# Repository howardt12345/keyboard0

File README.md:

# [keyboard0 project](https://kb.ht12345.xyz/0)
[![CC BY-NC-SA 4.0][cc-by-nc-sa-shield]][cc-by-nc-sa]

## This project is currently under active development. Everything is subject to change.

### Tenkeyless (TKL) hot-swap mechanical keyboard with macro keys column, 2 rotary encoders, and OLED display

The PCB is designed to use Kailh Hot-swap sockets. The original specifications also wanted a USB hub, which will be implemented through a separate USB hub daughterboard. 

---

[The layout on keyboard layout editor](http://www.keyboard-layout-editor.com/#/gists/689bc560553c37fa0d04dfba9f11ed96)

[Prototype 2 PCB photos on @howardt12345](https://www.instagram.com/p/CYXeXJdg_eP/)

[Details on my keyboard website](https://kb.ht12345.xyz/0)

[QMK Fork](https://github.com/howardt12345/qmk_firmware/tree/ht12345/keyboard0/keyboards/ht12345/keyboard0)

---
## All of the files in this repository, including the PCBs, are provided without liability and without any guarantee with regards to functionality. Any production files and prototypes from this project are provided without warranty of any kind.

---

**This work is licensed under a** [Creative Commons Attribution-NonCommercial-ShareAlike 4.0 International License][cc-by-nc-sa].

[![CC BY-NC-SA 4.0][cc-by-nc-sa-image]][cc-by-nc-sa]

[cc-by-nc-sa]: http://creativecommons.org/licenses/by-nc-sa/4.0/
[cc-by-nc-sa-image]: https://licensebuttons.net/l/by-nc-sa/4.0/88x31.png
[cc-by-nc-sa-shield]: https://img.shields.io/badge/License-CC%20BY--NC--SA%204.0-lightgrey.svg

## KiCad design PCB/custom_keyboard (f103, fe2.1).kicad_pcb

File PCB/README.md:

# keyboard0 PCB designs

## Directories: 

- `/p1`: The 1st prototype, ordered prototypes confirmed NOT working.
- `/p2`: The 2nd prototype, which I produced a batch of 2 prototypes and they worked (see respective readme)
- `/p3`: The 3rd prototype, under active development and NOT YET TESTED.
- `/Plate`: FR4 plate designs.

Any KiCad files in *this specific directory* is under active development and is subject to change. 

### These PCB designs are provided without liability and without any guarantee with regards to functionality. While I have personally tested some of the designs, I do not guarantee that they will work if you were to produce them yourself.

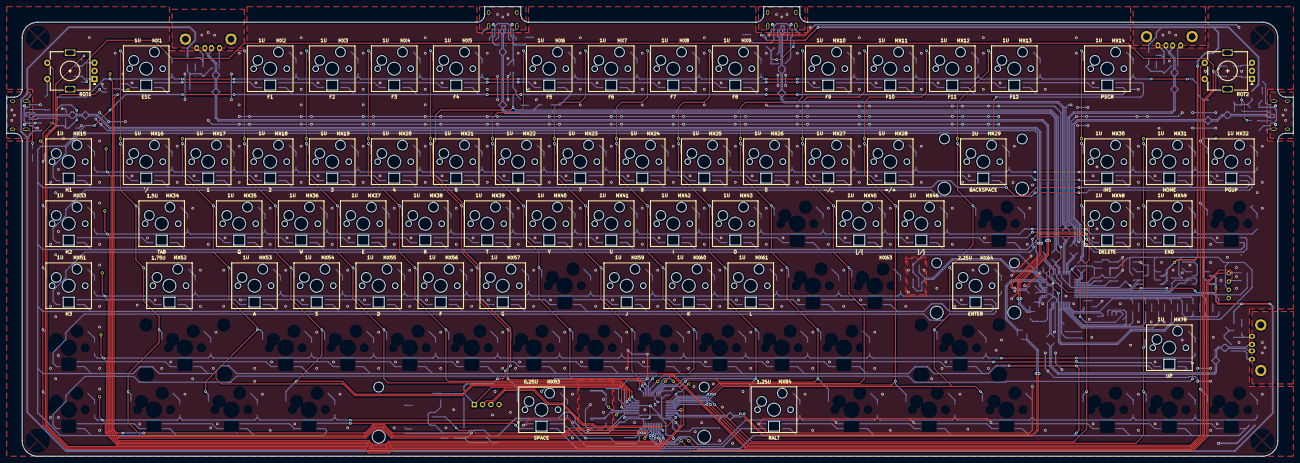
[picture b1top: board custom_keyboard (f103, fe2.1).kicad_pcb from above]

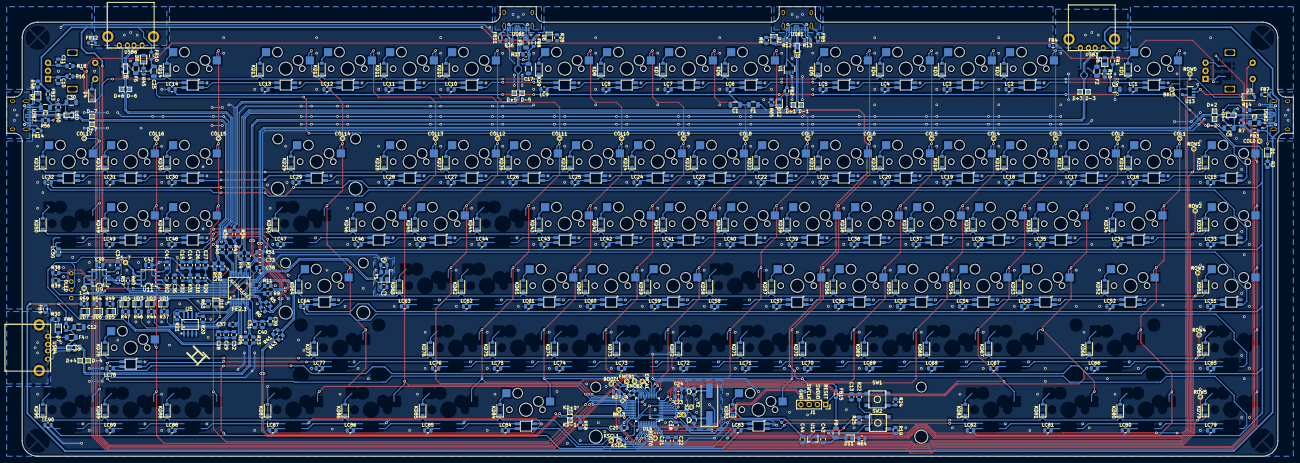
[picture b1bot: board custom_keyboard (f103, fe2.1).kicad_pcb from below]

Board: 2 copper layers, 395.3 x 138.1 mm, 468 parts (403 on the bottom side), 257 nets.

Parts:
1-4, 5-7: TestPoint_Small; TestPoint_THTPad_D1.0mm_Drill0.5mm
BKL3, BKL5: TestPoint_Small; TestPoint_THTPad_D1.0mm_Drill0.5mm
BOOT0, BOOT1: TestPoint_Small; TestPoint_THTPad_D1.0mm_Drill0.5mm
C1, C4, C6, C12, C17, C25, C30: 100uF; C_1206_3216Metric
C2, C5: 22pF; C_0805_2012Metric
C3, C7: 20pF; C_0805_2012Metric
C10, C11, C13, C14, C16, C18, C19, C20, C22, C26, C27, C28, C29, C31, C32, C33, C34, C35, C38, C39, C40, C41, C42: 100nF; C_0805_2012Metric
C15: 4.7uF; C_0805_2012Metric
C21, C36, C37: 10uF; C_0805_2012Metric
C23: 10nF; C_0805_2012Metric
C24, C43, C44: 1uF; C_0805_2012Metric
COL0, COL1, COL2, COL3, COL4, COL5, COL6, COL7, COL8, COL9, COL10, COL11, COL12, COL13, COL14, COL15, COL16, COL17: TestPoint_Small; TestPoint_THTPad_D1.0mm_Drill0.5mm
D1, D2, D5, D6, D7, D8, D9, D10, D11, D12: Red; LED_0805_2012Metric
D3, D4: SOD-123; D_SOD-123
D+1, D+2, D+3, D+4, D+5, D+6, D+7: TestPoint_Small; TestPoint_Pad_1.0x1.0mm
D-1, D-2, D-3, D-4, D-5, D-6, D-7: TestPoint_Small; TestPoint_Pad_1.0x1.0mm
ENCA1: TestPoint_Small; TestPoint_THTPad_D1.0mm_Drill0.5mm
ENCB1, ENCB2: TestPoint_Small; TestPoint_THTPad_D1.0mm_Drill0.5mm
F1, F2, F3, F4, F5, F6, F7, F8: 500mA; Fuse_1206_3216Metric
FB1, FB2, FB3, FB4, FB5, FB6, FB7, FB8, FB9, FB10, FB11, FB12, FB13, FB14, FB15: 60 @ 100 MHz; L_0805_2012Metric
FE2.1: FE2.1
J1: Conn_01x04; PinSocket_1x04_P2.54mm_Vertical
KD1, KD2, KD3, KD4, KD5, KD6, KD7, KD8, KD9, KD10, KD11, KD12, KD13, KD14, KD15, KD16, KD17, KD18, KD19, KD20, KD21, KD22, KD23, KD24, KD25, KD26, KD27, KD28, KD29, KD30, KD31, KD32, KD33, KD34, KD35, KD36, KD37, KD38, KD39, KD40, KD41, KD42, KD43, KD44, KD45, KD46, KD47, KD48, KD49, KD50, KD51, KD52, KD53, KD54, KD55, KD56, KD57, KD58, KD59, KD60, KD61, KD62, KD63, KD64, KD65, KD66, KD67, KD68, KD69, KD70, KD71, KD72, KD73, KD74, KD75, KD76, KD77, KD78, KD79, KD80, KD81, KD82, KD83, KD84, KD85, KD86, KD87, KD88, KD89, KD90: SOD-123; D_SOD-123
KD+1: TestPoint_Small; TestPoint_Pad_1.0x1.0mm
KD-1: TestPoint_Small; TestPoint_Pad_1.0x1.0mm
KSCL1: TestPoint_Small; TestPoint_THTPad_D1.0mm_Drill0.5mm
KSDA1: TestPoint_Small; TestPoint_THTPad_D1.0mm_Drill0.5mm
LC1, LC2, LC3, LC4, LC5, LC6, LC7, LC8, LC9, LC10, LC11, LC12, LC13, LC14, LC15, LC16, LC17, LC18, LC19, LC20, LC21, LC22, LC23, LC24, LC25, LC26, LC27, LC28, LC29, LC30, LC31, LC32, LC33, LC34, LC35, LC36, LC37, LC38, LC39, LC40, LC41, LC42, LC43, LC44, LC45, LC46, LC47, LC48, LC49, LC50, LC51, LC52, LC53, LC54, LC55, LC56, LC57, LC58, LC59, LC60, LC61, LC62, LC63, LC64, LC65, LC66, LC67, LC68, LC69, LC70, LC71, LC72, LC73, LC74, LC75, LC76, LC77, LC78, LC79, LC80, LC81, LC82, LC83, LC84, LC85, LC86, LC87, LC88, LC89, LC90: 10uF; C_0805_2012Metric
LOGO0: Logo; logo
MX1: ESC; CherryMX_1.00u_PCB_KailhSocket_LTST-A683CEGBW
MX2: F1; CherryMX_1.00u_PCB_KailhSocket_LTST-A683CEGBW
MX3: F2; CherryMX_1.00u_PCB_KailhSocket_LTST-A683CEGBW
MX4: F3; CherryMX_1.00u_PCB_KailhSocket_LTST-A683CEGBW
MX5: F4; CherryMX_1.00u_PCB_KailhSocket_LTST-A683CEGBW
MX6: F5; CherryMX_1.00u_PCB_KailhSocket_LTST-A683CEGBW
MX7: F6; CherryMX_1.00u_PCB_KailhSocket_LTST-A683CEGBW
MX8: F7; CherryMX_1.00u_PCB_KailhSocket_LTST-A683CEGBW
MX9: F8; CherryMX_1.00u_PCB_KailhSocket_LTST-A683CEGBW
MX10: F9; CherryMX_1.00u_PCB_KailhSocket_LTST-A683CEGBW
MX11: F10; CherryMX_1.00u_PCB_KailhSocket_LTST-A683CEGBW
MX12: F11; CherryMX_1.00u_PCB_KailhSocket_LTST-A683CEGBW
MX13: F12; CherryMX_1.00u_PCB_KailhSocket_LTST-A683CEGBW
MX14: PSCR; CherryMX_1.00u_PCB_KailhSocket_LTST-A683CEGBW
MX15: M1; CherryMX_1.00u_PCB_KailhSocket_LTST-A683CEGBW
MX16: `/~; CherryMX_1.00u_PCB_KailhSocket_LTST-A683CEGBW
MX17: 1; CherryMX_1.00u_PCB_KailhSocket_LTST-A683CEGBW
MX18: 2; CherryMX_1.00u_PCB_KailhSocket_LTST-A683CEGBW
MX19: 3; CherryMX_1.00u_PCB_KailhSocket_LTST-A683CEGBW
MX20: 4; CherryMX_1.00u_PCB_KailhSocket_LTST-A683CEGBW
MX21: 5; CherryMX_1.00u_PCB_KailhSocket_LTST-A683CEGBW
MX22: 6; CherryMX_1.00u_PCB_KailhSocket_LTST-A683CEGBW
MX23: 7; CherryMX_1.00u_PCB_KailhSocket_LTST-A683CEGBW
MX24: 8; CherryMX_1.00u_PCB_KailhSocket_LTST-A683CEGBW
MX25: 9; CherryMX_1.00u_PCB_KailhSocket_LTST-A683CEGBW
MX26: 0; CherryMX_1.00u_PCB_KailhSocket_LTST-A683CEGBW
MX27: -/_; CherryMX_1.00u_PCB_KailhSocket_LTST-A683CEGBW
MX28: =/+; CherryMX_1.00u_PCB_KailhSocket_LTST-A683CEGBW
MX29: BACKSPACE; CherryMX_2.00u_PCB_KailhSocket_LTST-A683CEGBW
MX30: INS; CherryMX_1.00u_PCB_KailhSocket_LTST-A683CEGBW
MX31: HOME; CherryMX_1.00u_PCB_KailhSocket_LTST-A683CEGBW
MX32: PGUP; CherryMX_1.00u_PCB_KailhSocket_LTST-A683CEGBW
MX33: M2; CherryMX_1.00u_PCB_KailhSocket_LTST-A683CEGBW
MX34: TAB; CherryMX_1.50u_PCB_KailhSocket_LTST-A683CEGBW
MX35: Q; CherryMX_1.00u_PCB_KailhSocket_LTST-A683CEGBW
MX36: W; CherryMX_1.00u_PCB_KailhSocket_LTST-A683CEGBW
MX37: E; CherryMX_1.00u_PCB_KailhSocket_LTST-A683CEGBW
MX38: R; CherryMX_1.00u_PCB_KailhSocket_LTST-A683CEGBW
MX39: T; CherryMX_1.00u_PCB_KailhSocket_LTST-A683CEGBW
MX40: Y; CherryMX_1.00u_PCB_KailhSocket_LTST-A683CEGBW
MX41: U; CherryMX_1.00u_PCB_KailhSocket_LTST-A683CEGBW
MX42: I; CherryMX_1.00u_PCB_KailhSocket_LTST-A683CEGBW
MX43: O; CherryMX_1.00u_PCB_KailhSocket_LTST-A683CEGBW
MX45: [/{; CherryMX_1.00u_PCB_KailhSocket_LTST-A683CEGBW
MX46: ]/}; CherryMX_1.00u_PCB_KailhSocket_LTST-A683CEGBW
MX48: DELETE; CherryMX_1.00u_PCB_KailhSocket_LTST-A683CEGBW
MX49: END; CherryMX_1.00u_PCB_KailhSocket_LTST-A683CEGBW
MX51: M3; CherryMX_1.00u_PCB_KailhSocket_LTST-A683CEGBW
MX52: CAPS; CherryMX_1.75u_PCB_KailhSocket_LTST-A683CEGBW
MX53: A; CherryMX_1.00u_PCB_KailhSocket_LTST-A683CEGBW
MX54: S; CherryMX_1.00u_PCB_KailhSocket_LTST-A683CEGBW
MX55: D; CherryMX_1.00u_PCB_KailhSocket_LTST-A683CEGBW
MX56: F; CherryMX_1.00u_PCB_KailhSocket_LTST-A683CEGBW
MX57: G; CherryMX_1.00u_PCB_KailhSocket_LTST-A683CEGBW
MX59: J; CherryMX_1.00u_PCB_KailhSocket_LTST-A683CEGBW
MX60: K; CherryMX_1.00u_PCB_KailhSocket_LTST-A683CEGBW
MX61: L; CherryMX_1.00u_PCB_KailhSocket_LTST-A683CEGBW
MX63: '/; CherryMX_1.00u_PCB_KailhSocket_LTST-A683CEGBW
MX64: ENTER; CherryMX_2.25u_PCB_KailhSocket_LTST-A683CEGBW
MX78: UP; CherryMX_1.00u_PCB_KailhSocket_LTST-A683CEGBW
MX83: SPACE; CherryMX_6.25u_PCB_KailhSocket_LTST-A683CEGBW
MX84: RALT; CherryMX_1.25u_PCB_KailhSocket_LTST-A683CEGBW
OL1: OLED; OLED_v2
R2, R8, R10, R24, R28, R30, R37, R44, R45, R46, R47, R48, R49, R54, R59, R63, R64, R65: 330; R_0805_2012Metric
R3, R4, R5, R6, R9, R11, R23, R26, R34, R35, R40, R41, R42, R43, R52, R53: 22; R_0805_2012Metric
R7, R14, R33, R36, R50, R56: 56K; R_0805_2012Metric
R12, R13: 5.1K; R_0805_2012Metric
R16, R18, R20, R21, R22, R25, R27, R38, R39: 10k; R_0805_2012Metric
R19: 1k; R_0805_2012Metric
R29, R32, R57, R60, R62: 100k; R_0603_1608Metric
R31: 47k; R_0805_2012Metric
R51: 2.7k; R_0805_2012Metric
R58: 1.5k; R_0805_2012Metric
ROT1, ROT2: Rotary_Encoder_Switch; RotaryEncoder_Alps_EC11E-Switch_Vertical_H20mm
ROW0, ROW1, ROW2, ROW3, ROW4, ROW5: TestPoint_Small; TestPoint_THTPad_D1.0mm_Drill0.5mm
SW1, SW2: SW_Push; SKQG-1155865
U1: SD00HA; SOT-23-5
U2, U4, U6, U8, U10: PRTR5V0U2X; SOT143B
U5: 24LC04BT-I/SN; 24LC04
U9, U11: MIC2505-1YM; MIC2505
U12: XC6206P332MR; SOT-23
U13: 74LVC1G34; SOT-23-5
U14: STM32F303CBTx; LQFP-48_7x7mm_P0.5mm
UD1, UD2, UD3, UD4, UD5, UD6, UD7: Green; LED_0805_2012Metric
USB1, USB2, USB5, USB7: HRO-TYPE-C-31-M-12; HRO-TYPE-C-31-M-12-Assembly
USB3, USB4, USB6: USB_A; USB-A-Generic
X1, X2: TestPoint_Small; TestPoint_THTPad_D1.0mm_Drill0.5mm
Y1: 12MHz; Crystal_SMD_3225-4Pin_3.2x2.5mm
Y2: 8MHz; Crystal_SMD_HC49-SD

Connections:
+1V8: C28.2, C29.2, C32.1, C37.1, FE2.1.6, FE2.1.25, FE2.1.28
+3V3: C18.1, C19.1, C20.1, C21.1, C22.1, C23.2, C24.1, C26.1, C27.1, C31.1, C33.2, C36.1, C38.2, C39.1, C40.1, C44.1, FE2.1.9, FE2.1.15, FE2.1.20, FE2.1.21, FE2.1.26, FE2.1.31, FE2.1.36, FE2.1.42, R19.1, R20.2, R21.1, R22.1, R29.1, R38.1, R39.1, R58.1, U5.7, U5.8, U12.2, U14.1, U14.9, U14.24, U14.36, U14.48
+5V: C1.1, C14.2, C15.2, C35.1, C42.1, F1.1, F1.2, FB2.1, FB15.2, FE2.1.8, LC1.2, LC2.2, LC3.2, LC4.2, LC5.2, LC6.2, LC7.2, LC8.2, LC9.2, LC10.2, LC11.2, LC12.2, LC13.2, LC14.2, LC15.2, LC16.2, LC17.2, LC18.2, LC19.2, LC20.2, LC21.2, LC22.2, LC23.2, LC24.2, LC25.2, LC26.2, LC27.2, LC28.2, LC29.2, LC30.2, LC31.2, LC32.2, LC33.2, LC34.2, LC35.2, LC36.2, LC37.2, LC38.2, LC39.2, LC40.2, LC41.2, LC42.2, LC43.2, LC44.2, LC45.2, LC46.2, LC47.2, LC48.2, LC49.2, LC50.2, LC51.2, LC52.2, LC53.2, LC54.2, LC55.2, LC56.2, LC57.2, LC58.2, LC59.2, LC60.2, LC61.2, LC62.2, LC63.2, LC64.2, LC65.2, LC66.2, LC67.2, LC68.2, LC69.2, LC70.2, LC71.2, LC72.2, LC73.2, LC74.2, LC75.2, LC76.2, LC77.2, LC78.2, LC79.2, LC80.2, LC81.2, LC82.2, LC83.2, LC84.2, LC85.2, LC86.2, LC87.2, LC88.2, LC89.2, LC90.2, MX1.6, MX2.6, MX3.6, MX4.6, MX5.6, MX6.6, MX7.6, MX8.6, MX9.6, MX10.6, MX11.6, MX12.6, MX13.6, MX14.6, MX15.6, MX16.6, MX17.6, MX18.6, MX19.6, MX20.6, MX21.6, MX22.6, MX23.6, MX24.6, MX25.6, MX26.6, MX27.6, MX28.6, MX29.6, MX30.6, MX31.6, MX32.6, MX33.6, MX34.6, MX35.6, MX36.6, MX37.6, MX38.6, MX39.6, MX40.6, MX41.6, MX42.6, MX43.6, MX45.6, MX46.6, MX48.6, MX49.6, MX51.6, MX52.6, MX53.6, MX54.6, MX55.6, MX56.6, MX57.6, MX59.6, MX60.6, MX61.6, MX64.6, MX78.6, MX83.6, MX84.6, OL1.3, R31.1, R57.1, R60.1, R62.1, U9.5, U9.7, U11.5, U11.7
BKL_DATA_IN: BKL5.1, U13.4
BKL_DATA_IN_3V3: BKL3.1, U13.2, U14.31
BOOT0: BOOT0.1, R25.1, SW2.2, U14.44
BOOT1: BOOT1.1, R27.2, U14.20
COL0: COL0.1, MX15.1, MX33.1, MX51.1, ROT1.S1, U14.3
COL1: COL1.1, MX1.1, MX16.1, MX34.1, MX52.1, U14.4
COL2: COL2.1, MX17.1, MX35.1, MX53.1, U14.2
COL3: COL3.1, MX2.1, MX18.1, MX36.1, MX54.1, U14.10
COL4: COL4.1, MX3.1, MX19.1, MX37.1, MX55.1, U14.11
COL5: COL5.1, MX4.1, MX20.1, MX38.1, MX56.1, U14.12
COL6: COL6.1, MX5.1, MX21.1, MX39.1, MX57.1, MX83.1, U14.13
COL7: COL7.1, MX6.1, MX22.1, MX40.1, U14.14
COL8: COL8.1, MX7.1, MX23.1, MX41.1, MX59.1, U14.15
COL9: COL9.1, MX8.1, MX24.1, MX42.1, MX60.1, U14.16
COL10: COL10.1, MX9.1, MX25.1, MX43.1, MX61.1, MX84.1, U14.21
COL11: COL11.1, MX10.1, MX26.1, U14.22
COL12: COL12.1, MX11.1, MX27.1, MX45.1, U14.25
COL13: COL13.1, MX12.1, MX28.1, MX46.1, U14.26
COL14: COL14.1, MX13.1, MX29.1, MX64.1, U14.27
COL15: COL15.1, MX14.1, MX30.1, MX48.1, U14.28
COL16: COL16.1, MX31.1, MX49.1, MX78.1, U14.29
COL17: COL17.1, MX32.1, ROT2.S1, U14.30
DOUT1: MX14.5, MX15.4
DOUT2: MX32.5, MX33.4
ENCODER_A: ENCA1.1, R16.2, U14.17
ENCODER_B1: ENCB1.1, U14.18
ENCODER_B2: ENCB2.1, R18.1, U14.19
Earth: FB4.2, FB5.2, FB7.1, FB9.2, FB11.1, FB12.2, FB14.1, USB1.13, USB2.13, USB3.5, USB4.5, USB5.13, USB6.5, USB7.13
GND: C1.2, C2.2, C3.2, C4.2, C5.2, C6.2, C7.2, C10.1, C11.2, C12.2, C13.2, C14.1, C15.1, C16.2, C17.2, C18.2, C19.2, C20.2, C21.2, C22.2, C23.1, C24.2, C25.2, C26.2, C27.2, C28.1, C29.1, C30.2, C31.2, C32.2, C33.1, C34.2, C35.2, C36.2, C37.2, C38.1, C39.2, C40.2, C41.2, C42.2, C43.2, C44.2, FB4.1, FB5.1, FB7.2, FB9.1, FB11.2, FB12.1, FB14.2, FE2.1.10, FE2.1.24, FE2.1.39, J1.4, LC1.1, LC2.1, LC3.1, LC4.1, LC5.1, LC6.1, LC7.1, LC8.1, LC9.1, LC10.1, LC11.1, LC12.1, LC13.1, LC14.1, LC15.1, LC16.1, LC17.1, LC18.1, LC19.1, LC20.1, LC21.1, LC22.1, LC23.1, LC24.1, LC25.1, LC26.1, LC27.1, LC28.1, LC29.1, LC30.1, LC31.1, LC32.1, LC33.1, LC34.1, LC35.1, LC36.1, LC37.1, LC38.1, LC39.1, LC40.1, LC41.1, LC42.1, LC43.1, LC44.1, LC45.1, LC46.1, LC47.1, LC48.1, LC49.1, LC50.1, LC51.1, LC52.1, LC53.1, LC54.1, LC55.1, LC56.1, LC57.1, LC58.1, LC59.1, LC60.1, LC61.1, LC62.1, LC63.1, LC64.1, LC65.1, LC66.1, LC67.1, LC68.1, LC69.1, LC70.1, LC71.1, LC72.1, LC73.1, LC74.1, LC75.1, LC76.1, LC77.1, LC78.1, LC79.1, LC80.1, LC81.1, LC82.1, LC83.1, LC84.1, LC85.1, LC86.1, LC87.1, LC88.1, LC89.1, LC90.1, MX1.3, MX2.3, MX3.3, MX4.3, MX5.3, MX6.3, MX7.3, MX8.3, MX9.3, MX10.3, MX11.3, MX12.3, MX13.3, MX14.3, MX15.3, MX16.3, MX17.3, MX18.3, MX19.3, MX20.3, MX21.3, MX22.3, MX23.3, MX24.3, MX25.3, MX26.3, MX27.3, MX28.3, MX29.3, MX30.3, MX31.3, MX32.3, MX33.3, MX34.3, MX35.3, MX36.3, MX37.3, MX38.3, MX39.3, MX40.3, MX41.3, MX42.3, MX43.3, MX45.3, MX46.3, MX48.3, MX49.3, MX51.3, MX52.3, MX53.3, MX54.3, MX55.3, MX56.3, MX57.3, MX59.3, MX60.3, MX61.3, MX64.3, MX78.3, MX83.3, MX84.3, OL1.4, R2.1, R8.1, R10.1, R12.2, R13.2, R24.1, R25.2, R27.1, R28.1, R30.1, R32.2, R45.1, R48.1, R51.1, R63.1, R64.1, R65.1, ROT1.C, ROT2.C, U1.2, U2.1, U4.1, U5.1, U5.2, U5.3, U5.4, U6.1, U8.1, U9.3, U10.1, U11.3, U12.1, U13.3, U14.8, U14.23, U14.35, U14.47, USB1.1, USB1.12, USB2.1, USB2.12, USB3.4, USB4.4, USB5.1, USB5.12, USB6.4, USB7.1, USB7.12, Y1.2, Y1.4
HUB_D+: FE2.1.30, R4.2
HUB_D-: FE2.1.29, R3.2
HUB_DRV: D10.2, FE2.1.1, UD1.2, UD2.2, UD3.2, UD4.2, UD5.2, UD6.2, UD7.2
HUB_LED1: FE2.1.3, R21.2, R37.2, U5.6
HUB_LED2: FE2.1.4, R44.2
HUB_LED3: FE2.1.5, R46.2
HUB_LED4: FE2.1.7, R47.2
HUB_LED5: FE2.1.48, R49.2
HUB_LED6: FE2.1.47, R54.2
HUB_LED7: FE2.1.46, R59.2
HUB_PORT1_D+: FE2.1.19, R43.1
HUB_PORT1_D-: FE2.1.18, R41.1
HUB_PORT2_D+: FE2.1.17, R11.2
HUB_PORT2_D-: FE2.1.16, R9.2
HUB_PORT3_D+: FE2.1.14, R5.2
HUB_PORT3_D-: FE2.1.13, R6.2
HUB_PORT4_D+: FE2.1.12, R23.2
HUB_PORT4_D-: FE2.1.11, R26.2
HUB_PORT5_D+: FE2.1.33, R35.1
HUB_PORT5_D-: FE2.1.32, R34.1
HUB_PORT6_D+: FE2.1.35, R40.2
HUB_PORT6_D-: FE2.1.34, R42.2
HUB_PORT7_D+: FE2.1.38, R53.2
HUB_PORT7_D-: FE2.1.37, R52.2
HUB_SDA: FE2.1.2, R20.1, U5.5
HUB_XIN: C2.1, FE2.1.22, Y1.1
HUB_XOUT: C5.1, FE2.1.23, Y1.3
KEYBOARD_5V: C43.1, D11.2, F8.1, U12.3, U13.5
KEYBOARD_D+: KD-1.1, R43.2, R58.2, U14.33
KEYBOARD_D-: KD+1.1, R41.2, U14.32
KEYBOARD_RESET: C13.1, J1.1, R22.2, SW1.2, U14.7
KEYBOARD_SCL: KSCL1.1, OL1.2, R39.2, U14.42
KEYBOARD_SDA: KSDA1.1, OL1.1, R38.2, U14.43
KEYBOARD_XTAL1: C3.1, U14.5, X1.1, Y2.1
KEYBOARD_XTAL2: C7.1, U14.6, X2.1, Y2.2
unnamed: C4.1, F2.2, FB1.2
unnamed: C6.1, F3.1, FB3.2, R7.1, R14.1, U4.4
unnamed: C10.2, R16.1, ROT2.A
unnamed: C11.1, R18.2, ROT2.B
unnamed: C12.1, F4.2, FB6.2, U6.4
unnamed: C17.1, F5.1, FB8.2, R33.1, R36.1
unnamed: C25.1, F6.2, FB10.2, U8.4
unnamed: C30.1, F7.1, FB13.2, R50.1, R56.1, U10.4
unnamed: C34.1, U9.4
unnamed: C41.1, U11.4
unnamed: D1.1, R2.2
unnamed: D1.2, F3.2, USB2.2, USB2.11
unnamed: D2.1, R8.2
unnamed: D3.2, ROT1.S2
unnamed: D4.2, ROT2.S2
unnamed: D5.1, R10.2
unnamed: D5.2, F2.1, USB3.1
unnamed: D6.1, R28.2
unnamed: D6.2, F5.2, USB5.2, USB5.11
unnamed: D7.1, R30.2
unnamed: D7.2, F4.1, USB4.1
unnamed: D8.1, R45.2
unnamed: D8.2, F6.1, USB6.1
unnamed: D9.1, R48.2
unnamed: D9.2, F7.2, USB7.2, USB7.11
unnamed: D10.1, R63.2
unnamed: D11.1, R64.2
unnamed: D12.1, R65.2
unnamed: D12.2, FB2.2, U1.1
unnamed: D+1.1, R4.1, U2.2, USB1.6, USB1.8
unnamed: D+2.1, R11.1, U4.2, USB2.6, USB2.8
unnamed: D+3.1, R5.1, USB3.3
unnamed: D+4.1, R23.1, U6.2, USB4.3
unnamed: D+5.1, R35.2, USB5.6, USB5.8
unnamed: D+6.1, R40.1, U8.2, USB6.3
unnamed: D+7.1, R53.1, U10.2, USB7.6, USB7.8
unnamed: D-1.1, R3.1, U2.3, USB1.5, USB1.7
unnamed: D-2.1, R9.1, U4.3, USB2.5, USB2.7
unnamed: D-3.1, R6.1, USB3.2
unnamed: D-4.1, R26.1, U6.3, USB4.2
unnamed: D-5.1, R34.2, USB5.5, USB5.7
unnamed: D-6.1, R42.1, U8.3, USB6.2
unnamed: D-7.1, R52.1, U10.3, USB7.5, USB7.7
unnamed: F8.2, FB15.1
unnamed: FE2.1.27, R51.2
unnamed: KD1.2, MX1.2
unnamed: KD2.2, MX2.2
unnamed: KD3.2, MX3.2
unnamed: KD4.2, MX4.2
unnamed: KD5.2, MX5.2
unnamed: KD6.2, MX6.2
unnamed: KD7.2, MX7.2
unnamed: KD8.2, MX8.2
unnamed: KD9.2, MX9.2
unnamed: KD10.2, MX10.2
unnamed: KD11.2, MX11.2
unnamed: KD12.2, MX12.2
unnamed: KD13.2, MX13.2
unnamed: KD14.2, MX14.2
unnamed: KD15.2, MX15.2
unnamed: KD16.2, MX16.2
unnamed: KD17.2, MX17.2
unnamed: KD18.2, MX18.2
unnamed: KD19.2, MX19.2
unnamed: KD20.2, MX20.2
unnamed: KD21.2, MX21.2
unnamed: KD22.2, MX22.2
unnamed: KD23.2, MX23.2
unnamed: KD24.2, MX24.2
unnamed: KD25.2, MX25.2
unnamed: KD26.2, MX26.2
unnamed: KD27.2, MX27.2
unnamed: KD28.2, MX28.2
unnamed: KD29.2, MX29.2
unnamed: KD30.2, MX30.2
unnamed: KD31.2, MX31.2
unnamed: KD32.2, MX32.2
unnamed: KD33.2, MX33.2
unnamed: KD34.2, MX34.2
unnamed: KD35.2, MX35.2
unnamed: KD36.2, MX36.2
unnamed: KD37.2, MX37.2
unnamed: KD38.2, MX38.2
unnamed: KD39.2, MX39.2
unnamed: KD40.2, MX40.2
unnamed: KD41.2, MX41.2
unnamed: KD42.2, MX42.2
unnamed: KD43.2, MX43.2
unnamed: KD45.2, MX45.2
unnamed: KD46.2, MX46.2
unnamed: KD48.2, MX48.2
unnamed: KD49.2, MX49.2
unnamed: KD51.2, MX51.2
unnamed: KD52.2, MX52.2
unnamed: KD53.2, MX53.2
unnamed: KD54.2, MX54.2
unnamed: KD55.2, MX55.2
unnamed: KD56.2, MX56.2
unnamed: KD57.2, MX57.2
unnamed: KD59.2, MX59.2
unnamed: KD60.2, MX60.2
unnamed: KD61.2, MX61.2
unnamed: KD64.2, MX64.2
unnamed: KD78.2, MX78.2
unnamed: KD83.2, MX83.2
unnamed: KD84.2, MX84.2
unnamed: MX1.5, MX2.4
unnamed: MX2.5, MX3.4
unnamed: MX3.5, MX4.4
unnamed: MX4.5, MX5.4
unnamed: MX5.5, MX6.4
unnamed: MX6.5, MX7.4
unnamed: MX7.5, MX8.4
unnamed: MX8.5, MX9.4
unnamed: MX9.5, MX10.4
unnamed: MX10.5, MX11.4
unnamed: MX11.5, MX12.4
unnamed: MX12.5, MX13.4
unnamed: MX13.5, MX14.4
unnamed: MX15.5, MX16.4
unnamed: MX16.5, MX17.4
unnamed: MX17.5, MX18.4
unnamed: MX18.5, MX19.4
unnamed: MX19.5, MX20.4
unnamed: MX20.5, MX21.4
unnamed: MX21.5, MX22.4
unnamed: MX22.5, MX23.4
unnamed: MX23.5, MX24.4
unnamed: MX24.5, MX25.4
unnamed: MX25.5, MX26.4
unnamed: MX26.5, MX27.4
unnamed: MX27.5, MX28.4
unnamed: MX28.5, MX29.4
unnamed: MX29.5, MX30.4
unnamed: MX30.5, MX31.4
unnamed: MX31.5, MX32.4
unnamed: MX33.5, MX34.4
unnamed: MX34.5, MX35.4
unnamed: MX35.5, MX36.4
unnamed: MX36.5, MX37.4
unnamed: MX37.5, MX38.4
unnamed: MX38.5, MX39.4
unnamed: MX39.5, MX40.4
unnamed: MX40.5, MX41.4
unnamed: MX41.5, MX42.4
unnamed: MX42.5, MX43.4
unnamed: MX45.5, MX46.4
unnamed: MX48.5, MX49.4
unnamed: MX51.5, MX52.4
unnamed: MX52.5, MX53.4
unnamed: MX53.5, MX54.4
unnamed: MX54.5, MX55.4
unnamed: MX55.5, MX56.4
unnamed: MX56.5, MX57.4
unnamed: MX59.5, MX60.4
unnamed: MX60.5, MX61.4
unnamed: MX83.5, MX84.4
unnamed: R7.2, USB2.4
unnamed: R12.1, USB1.10
unnamed: R13.1, USB1.4
unnamed: R14.2, USB2.10
unnamed: R19.2, SW2.1
unnamed: R24.2, SW1.1
unnamed: R33.2, USB5.4
unnamed: R36.2, USB5.10
unnamed: R37.1, UD1.1
unnamed: R44.1, UD2.1
unnamed: R46.1, UD3.1
unnamed: R47.1, UD4.1
unnamed: R49.1, UD5.1
unnamed: R50.2, USB7.4
unnamed: R54.1, UD6.1
unnamed: R56.2, USB7.10
unnamed: R59.1, UD7.1
OVCJ1: FE2.1.45, R57.2, U9.2
OVCJ5: FE2.1.43, R62.2, U11.2
PORT1-4_PWR: 1-4.1, FB1.1, FB3.1, FB6.1, U9.6, U9.8
PORT5-7PWR: 5-7.1, FB8.1, FB10.1, FB13.1, U11.6, U11.8
PWRJ: FE2.1.44, R60.2, U9.1, U11.1
ROT1_ROW: D3.1, D4.1, KD1.1, KD2.1, KD3.1, KD4.1, KD5.1, KD6.1, KD7.1, KD8.1, KD9.1, KD10.1, KD11.1, KD12.1, KD13.1, KD14.1, ROW0.1, U14.46
ROW1: KD15.1, KD16.1, KD17.1, KD18.1, KD19.1, KD20.1, KD21.1, KD22.1, KD23.1, KD24.1, KD25.1, KD26.1, KD27.1, KD28.1, KD29.1, KD30.1, KD31.1, KD32.1, ROW1.1, U14.45
ROW2: KD33.1, KD34.1, KD35.1, KD36.1, KD37.1, KD38.1, KD39.1, KD40.1, KD41.1, KD42.1, KD43.1, KD44.1, KD45.1, KD46.1, KD47.1, KD48.1, KD49.1, KD50.1, ROW2.1, U14.41
ROW3: KD51.1, KD52.1, KD53.1, KD54.1, KD55.1, KD56.1, KD57.1, KD58.1, KD59.1, KD60.1, KD61.1, KD62.1, KD63.1, KD64.1, ROW3.1, U14.40
ROW4: KD65.1, KD66.1, KD67.1, KD68.1, KD69.1, KD70.1, KD71.1, KD72.1, KD73.1, KD74.1, KD75.1, KD76.1, KD77.1, KD78.1, ROW4.1, U14.39
ROW5: KD79.1, KD80.1, KD81.1, KD82.1, KD83.1, KD84.1, KD85.1, KD86.1, KD87.1, KD88.1, KD89.1, KD90.1, ROW5.1, U14.38
SWCLK: J1.3, U14.37
SWDIO: J1.2, U14.34
VBUS: D2.2, U1.4, U1.5, U2.4, USB1.2, USB1.11
VBUSM: FE2.1.41, R31.2, R32.1
XRSTJ: C16.1, FE2.1.40, R29.2

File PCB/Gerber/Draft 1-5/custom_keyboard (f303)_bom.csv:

Comment,Designator,Footprint,LCSC Part #
"100uF Unpolarized capacitor, small symbol","C1,C4,C6,C12,C17,C25,C30",C_1206_3216Metric,C15008
"22pF Unpolarized capacitor, small symbol","C2,C5",C_0805_2012Metric,C1804
"20pF Unpolarized capacitor, small symbol","C3,C7",C_0805_2012Metric,C1798
"100nF Unpolarized capacitor, small symbol","C8,C9,C10,C11,C13,C14,C16,C18,C19,C20,C22,C26,C27,C28,C29,C31,C32,C33,C34,C35,C38,C39,C40,C41,C42",C_0805_2012Metric,C49678
"4.7uF Unpolarized capacitor, small symbol",C15,C_0805_2012Metric,C1779
"10uF Unpolarized capacitor, small symbol","C21,C36,C37",C_0805_2012Metric,C15850
"10nF Unpolarized capacitor, small symbol",C23,C_0805_2012Metric,C1710
"1uF Unpolarized capacitor, small symbol","C24,C43,C44",C_0805_2012Metric,C28323
"Red Light emitting diode, small symbol","D1,D2,D5,D6,D7,D8,D9,D10,D11,D12",LED_0805_2012Metric,C84256
"SOD-123 Diode, small symbol","D3,D4",D_SOD-123,C81598
"500mA Resettable fuse, polymeric positive temperature coefficient, small symbol","F1,F2,F3,F4,F5,F6,F7,F8",Fuse_1206_3216Metric,C70069
"60 @ 100 MHz Ferrite bead, small symbol","FB1,FB2,FB3,FB4,FB5,FB6,FB7,FB8,FB9,FB10,FB11,FB12,FB13,FB14,FB15",L_0805_2012Metric,C237300
FE2.1 ,FE2.1,FE2.1,C39693
"SOD-123 Diode, small symbol","KD1,KD2,KD3,KD4,KD5,KD6,KD7,KD8,KD9,KD10,KD11,KD12,KD13,KD14,KD15,KD16,KD17,KD18,KD19,KD20,KD21,KD22,KD23,KD24,KD25,KD26,KD27,KD28,KD29,KD30,KD31,KD32,KD33,KD34,KD35,KD36,KD37,KD38,KD39,KD40,KD41,KD42,KD43,KD44,KD45,KD46,KD47,KD48,KD49,KD50,KD51,KD52,KD53,KD54,KD55,KD56,KD57,KD58,KD59,KD60,KD61,KD62,KD63,KD64,KD65,KD66,KD67,KD68,KD69,KD70,KD71,KD72,KD73,KD74,KD75,KD76,KD77,KD78,KD79,KD80,KD81,KD82,KD83,KD84,KD85,KD86,KD87,KD88,KD89,KD90",D_SOD-123,C81598
"10uF Unpolarized capacitor, small symbol","LC1,LC2,LC3,LC4,LC5,LC6,LC7,LC8,LC9,LC10,LC11,LC12,LC13,LC14,LC15,LC16,LC17,LC18,LC19,LC20,LC21,LC22,LC23,LC24,LC25,LC26,LC27,LC28,LC29,LC30,LC31,LC32,LC33,LC34,LC35,LC36,LC37,LC38,LC39,LC40,LC41,LC42,LC43,LC44,LC45,LC46,LC47,LC48,LC49,LC50,LC51,LC52,LC53,LC54,LC55,LC56,LC57,LC58,LC59,LC60,LC61,LC62,LC63,LC64,LC65,LC66,LC67,LC68,LC69,LC70,LC71,LC72,LC73,LC74,LC75,LC76,LC77,LC78,LC79,LC80,LC81,LC82,LC83,LC84,LC85,LC86,LC87,LC88,LC89,LC90",C_0805_2012Metric,C15850
"470 Resistor, small symbol",R1,R_0805_2012Metric,C17710
"330 Resistor, small symbol","R2,R8,R10,R24,R28,R30,R37,R44,R45,R46,R47,R48,R49,R54,R59,R63,R64,R65",R_0805_2012Metric,C17630
"22 Resistor, small symbol","R3,R4,R5,R6,R9,R11,R23,R26,R34,R35,R40,R41,R42,R43,R52,R53",R_0805_2012Metric,C17561
"56K Resistor, small symbol","R7,R14,R33,R36,R50,R56",R_0805_2012Metric,C17756
"5.1K Resistor, small symbol","R12,R13",R_0805_2012Metric,C27834
"10k Resistor, small symbol","R15,R16,R17,R18,R20,R21,R22,R25,R27,R38,R39",R_0805_2012Metric,C17414
"1k Resistor, small symbol",R19,R_0805_2012Metric,C17513
"100k Resistor, small symbol","R29,R32,R57,R60,R62",R_0603_1608Metric,C25803
"47k Resistor, small symbol",R31,R_0805_2012Metric,C17713
"2.7k Resistor, small symbol",R51,R_0805_2012Metric,C17530
"1.5k Resistor, small symbol",R58,R_0805_2012Metric,C4310
"SW_Push Push button switch, generic, two pins","SW1,SW2",SKQG-1155865,C318884
"SD00HA Current limited 3A power switch, single channel, SOT-23-5",U1,SOT-23-5,C521425
PRTR5V0U2X ,"U2,U3,U4,U6,U7,U8,U10",SOT143B,C2827688
"24LC04BT-I/SN I2C Serial EEPROM, 2Kb, DIP-8/SOIC-8/TSSOP-8/DFN-8",U5,24LC04,C511263
MIC2505-1YM ,"U9,U11",MIC2505,C219158
"XC6206P332MR Positive 60-250mA Low Dropout Regulator, Fixed Output, SOT-23",U12,SOT-23,C5446
"74LVC1G34 Single Buffef Gate, Low-Voltage CMOS",U13,SOT-23-5,C526347
"STM32F303CBT6 ARM Cortex-M4 MCU, 128KB flash, 32KB RAM, 72MHz, 2-3.6V, 37 GPIO, LQFP-48",U14,LQFP-48_7x7mm_P0.5mm,C108516
"Green Light emitting diode, small symbol","UD1,UD2,UD3,UD4,UD5,UD6,UD7",LED_0805_2012Metric,C2297
HRO-TYPE-C-31-M-12 ,"USB1,USB2,USB5,USB7",HRO-TYPE-C-31-M-12-Assembly,C165948
"12MHz Four pin crystal, GND on pins 2 and 4, small symbol",Y1,Crystal_SMD_3225-4Pin_3.2x2.5mm,C9002
"8MHz Two pin crystal, small symbol",Y2,Crystal_SMD_HC49-SD,C12674

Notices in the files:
PCB/custom_keyboard (f103, fe2.1).kicad_pcb:
© 2021 Howard Tseng
